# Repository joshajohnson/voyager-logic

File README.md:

# Voyager Logic

A FX3 based logic analyser capable of 16 channels at 100 MSPS.

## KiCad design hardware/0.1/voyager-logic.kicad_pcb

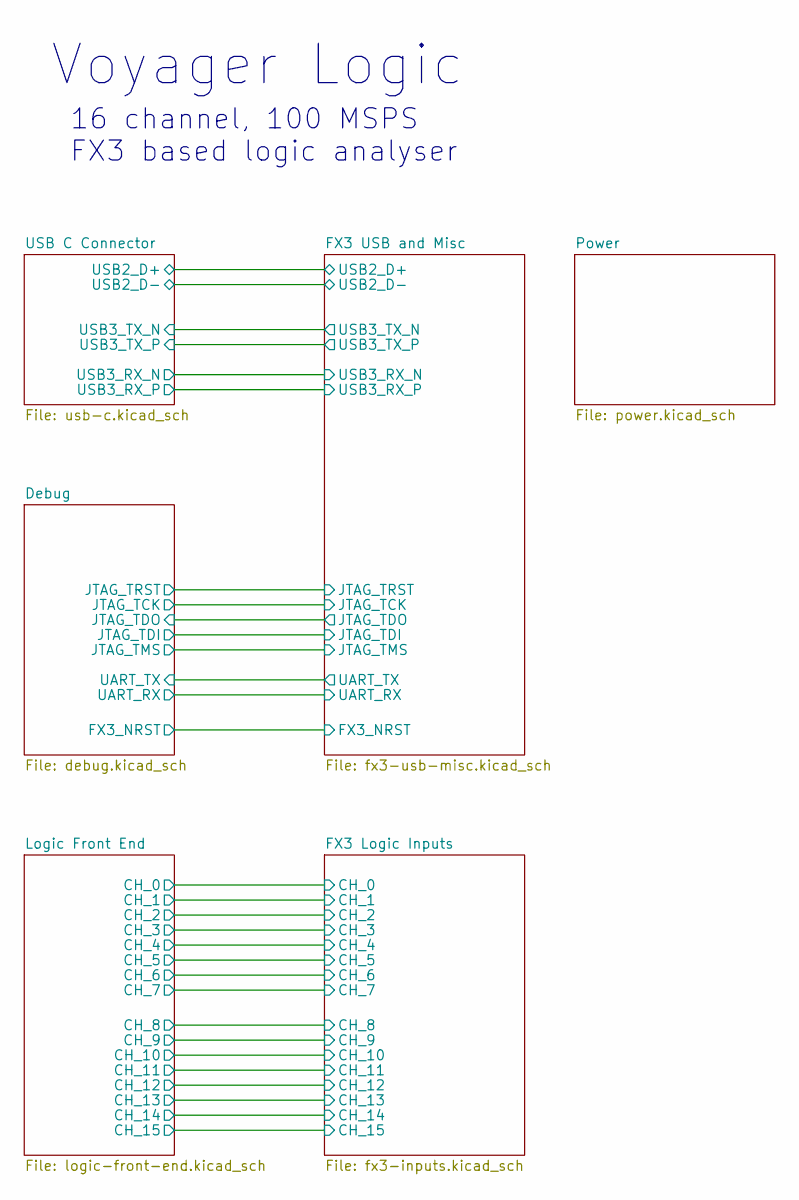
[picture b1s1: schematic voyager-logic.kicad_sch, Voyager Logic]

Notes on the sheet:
16 channel, 100 MSPS FX3 based logic analyser
Voyager Logic

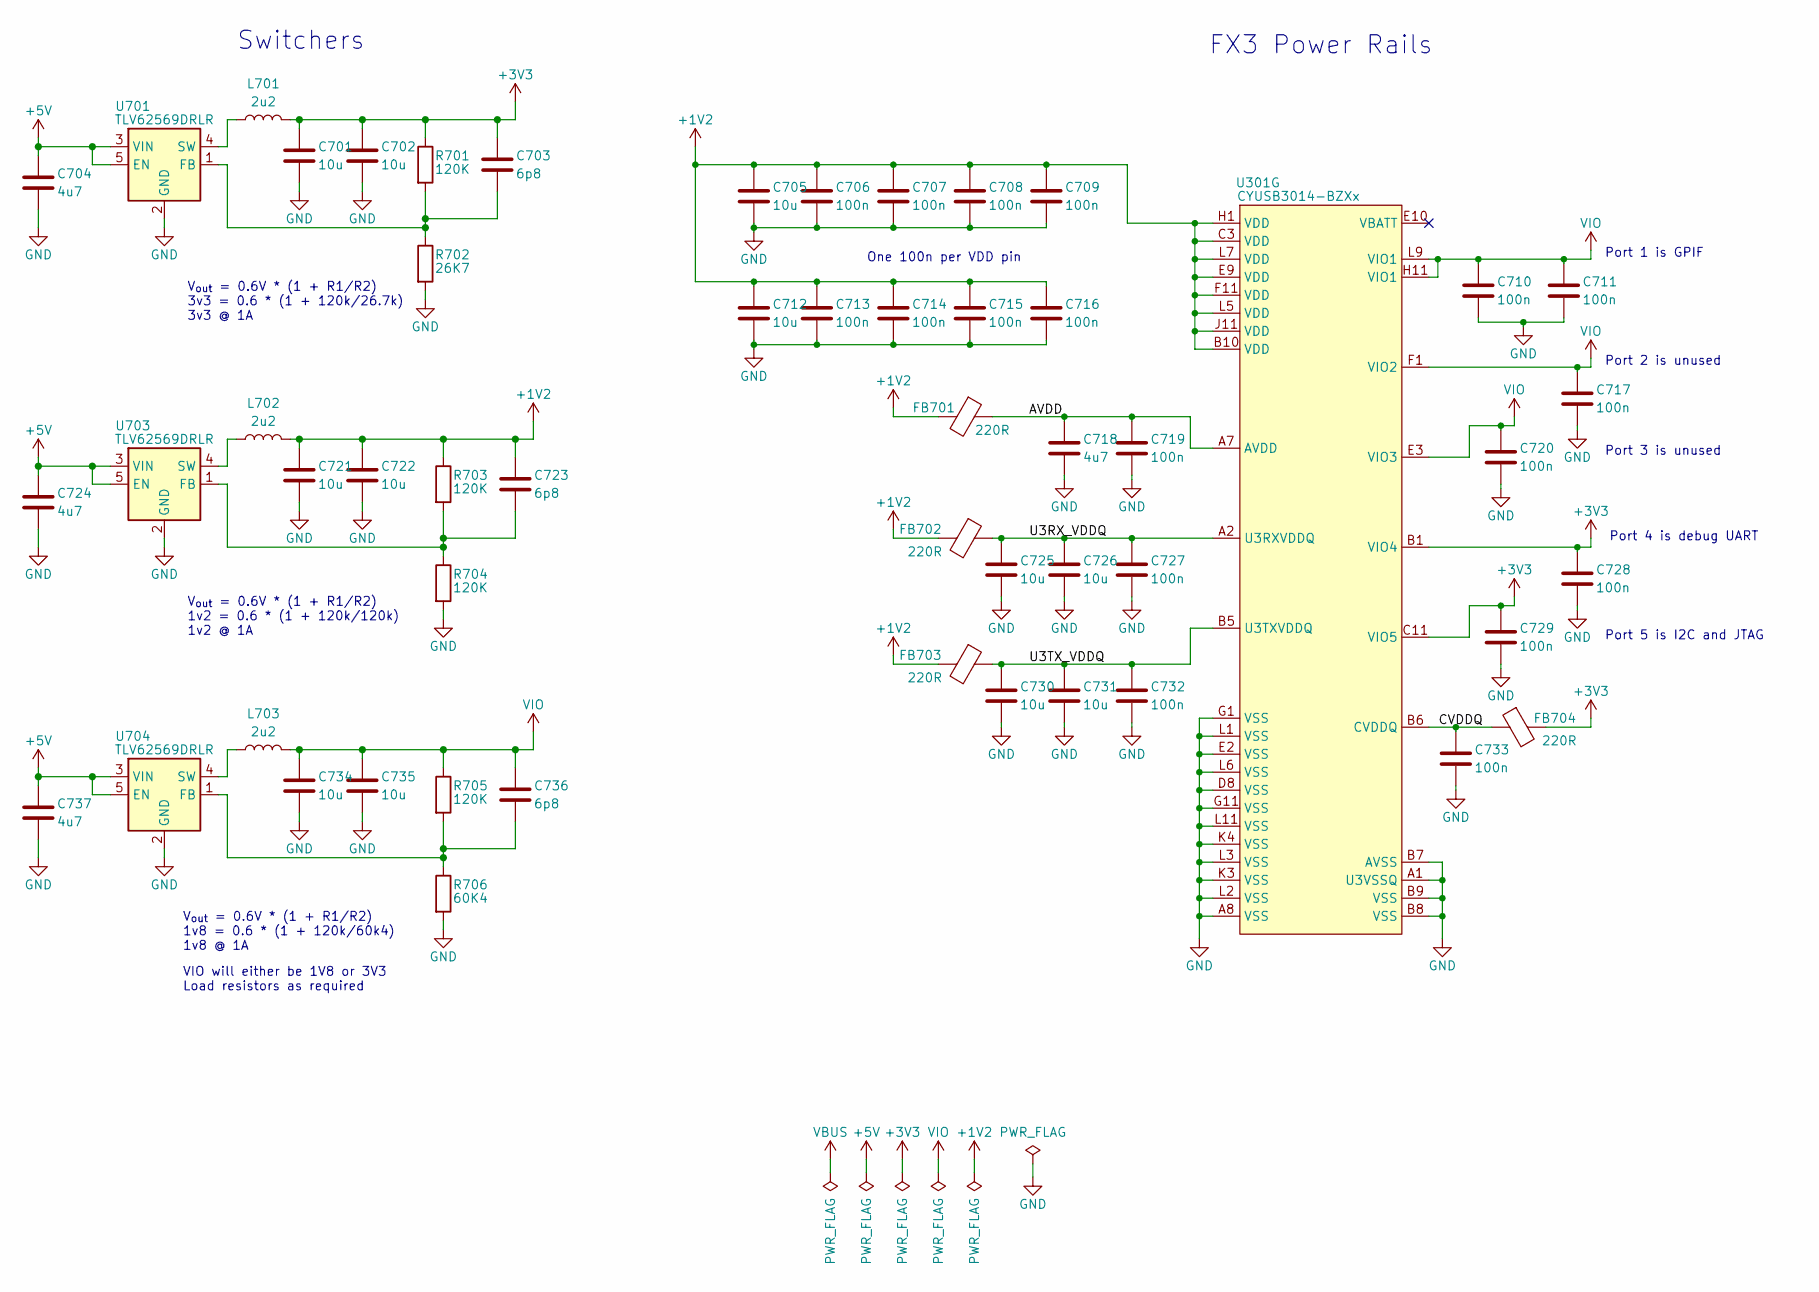
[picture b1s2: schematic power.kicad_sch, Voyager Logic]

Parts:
C701, C702, C705, C712, C721, C722, C725, C726, C730, C731, C734, C735: 10u; C_0603_1608Metric; MPN CL10A106MA8NRNC; LCSC C96446
C703, C723, C736: 6p8; C_0402_1005Metric; MPN GJM1555C1H6R8BB01D; LCSC C88896
C704, C718, C724, C737: 4u7; C_0402_1005Metric; MPN CL05A475MP5NRNC; LCSC C23733
C706, C707, C708, C709, C710, C711, C713, C714, C715, C716, C717, C719, C720, C727, C728, C729, C732, C733: 100n; C_0402_1005Metric; MPN CL05B104KB54PNC; LCSC C307331
FB701, FB702, FB703, FB704: 220R; R_0402_1005Metric; MPN BLM15PX221SN1D; LCSC C160973
L701, L702, L703: 2u2; L_0805_2012Metric; MPN LQM21PN2R2NGCD; LCSC C216156
R701, R703, R704, R705: 120K; R_0402_1005Metric; MPN RC0402FR-07120KL; LCSC C93945
R702: 26K7; R_0402_1005Metric; MPN RC0402FR-0726K7L; LCSC C138023
R706: 60K4; R_0402_1005Metric; MPN RC0402FR-0760K4L; LCSC C327333
U301: CYUSB3014-BZXx; BGA-121_10x10mm_Layout11x11_P0.8mm; MPN CYUSB3014-BZXC; LCSC C462526
U701, U703, U704: TLV62569DRLR; SOT-563; MPN TLV62569DRLR; LCSC C163217

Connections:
+1V2: C705.1, C706.1, C707.1, C708.1, C709.1, C712.1, C713.1, C714.1, C715.1, C716.1, C721.1, C722.1, C723.1, FB701.2, FB702.2, FB703.2, L702.2, R703.1, U301.B10 (VDD), U301.C3 (VDD), U301.E9 (VDD), U301.F11 (VDD), U301.H1 (VDD), U301.J11 (VDD), U301.L5 (VDD), U301.L7 (VDD)
+3V3: C701.1, C702.1, C703.1, C728.1, C729.1, FB704.2, L701.2, R701.1, U301.B1 (VIO4), U301.C11 (VIO5); also elsewhere on the board
+5V: C704.1, C724.1, C737.1, U701.3 (VIN), U701.5 (EN), U703.3 (VIN), U703.5 (EN), U704.3 (VIN), U704.5 (EN); also elsewhere on the board
/Power/AVDD: C718.1, C719.1, FB701.1, U301.A7 (AVDD)
/Power/CVDDQ: C733.1, FB704.1, U301.B6 (CVDDQ)
/Power/U3RX_VDDQ: C725.1, C726.1, C727.1, FB702.1, U301.A2 (U3RXVDDQ)
/Power/U3TX_VDDQ: C730.1, C731.1, C732.1, FB703.1, U301.B5 (U3TXVDDQ)
GND: C701.2, C702.2, C704.2, C705.2, C706.2, C707.2, C708.2, C709.2, C710.2, C711.2, C712.2, C713.2, C714.2, C715.2, C716.2, C717.2, C718.2, C719.2, C720.2, C721.2, C722.2, C724.2, C725.2, C726.2, C727.2, C728.2, C729.2, C730.2, C731.2, C732.2, C733.2, C734.2, C735.2, C737.2, R702.2, R704.2, R706.2, U301.A1 (U3VSSQ), U301.A8 (VSS), U301.B7 (AVSS), U301.B8 (VSS), U301.B9 (VSS), U301.D8 (VSS), U301.E2 (VSS), U301.G1 (VSS), U301.G11 (VSS), U301.K3 (VSS), U301.K4 (VSS), U301.L1 (VSS), U301.L2 (VSS), U301.L3 (VSS), U301.L6 (VSS), U301.L11 (VSS), U701.2 (GND), U703.2 (GND), U704.2 (GND); also elsewhere on the board
unnamed: C703.2, R701.2, R702.1, U701.1 (FB)
unnamed: C723.2, R703.2, R704.1, U703.1 (FB)
unnamed: C736.2, R705.2, R706.1, U704.1 (FB)
unnamed: L701.1, U701.4 (SW)
unnamed: L702.1, U703.4 (SW)
unnamed: L703.1, U704.4 (SW)
VIO: C710.1, C711.1, C717.1, C720.1, C734.1, C735.1, C736.1, L703.2, R705.1, U301.E3 (VIO3), U301.F1 (VIO2), U301.H11 (VIO1), U301.L9 (VIO1); also elsewhere on the board

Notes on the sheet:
V_{out} = 0.6V * (1 + R1/R2) 3v3 = 0.6 * (1 + 120k/26.7k) 3v3 @ 1A
V_{out} = 0.6V * (1 + R1/R2) 1v8 = 0.6 * (1 + 120k/60k4) 1v8 @ 1A
Switchers
FX3 Power Rails
Port 2 is unused
Port 4 is debug UART
One 100n per VDD pin
Port 3 is unused
V_{out} = 0.6V * (1 + R1/R2) 1v2 = 0.6 * (1 + 120k/120k) 1v2 @ 1A
Port 1 is GPIF
Port 5 is I2C and JTAG
VIO will either be 1V8 or 3V3 Load resistors as required

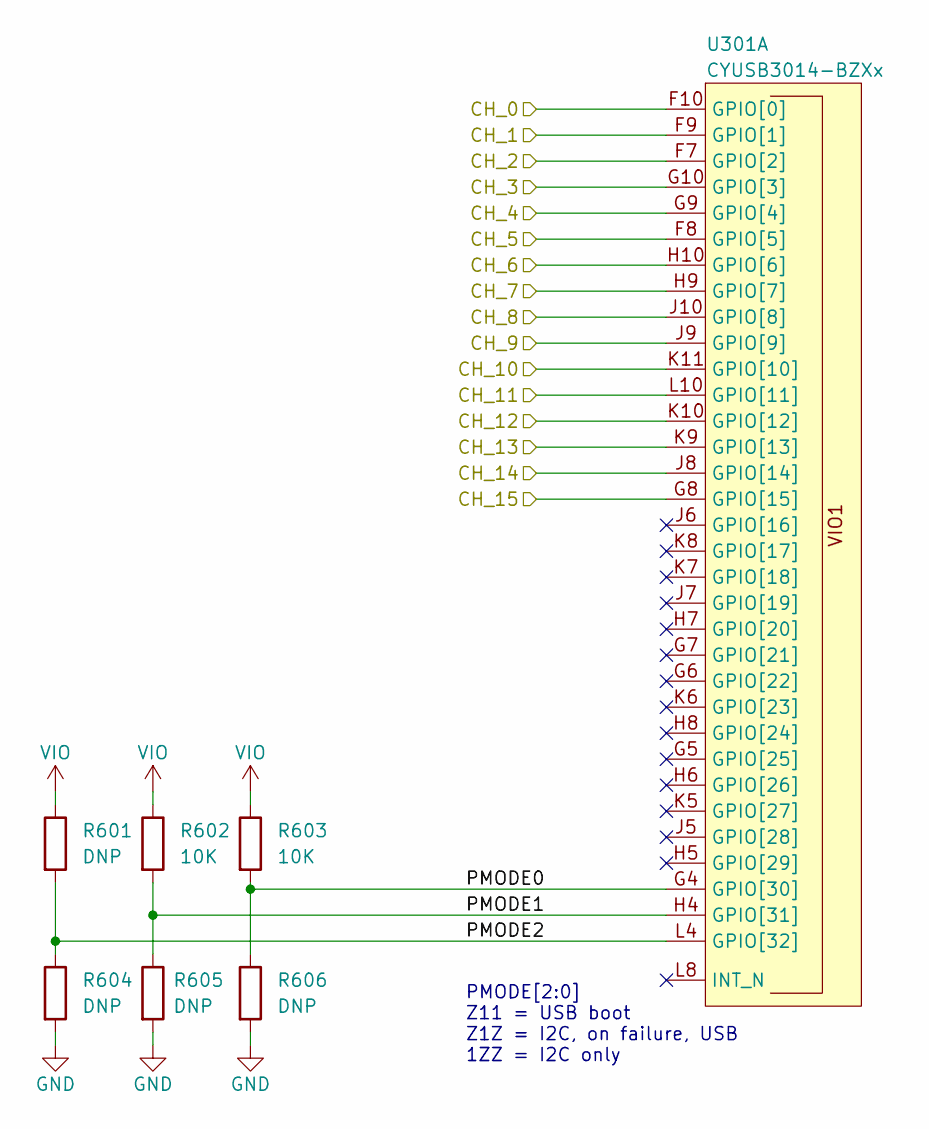
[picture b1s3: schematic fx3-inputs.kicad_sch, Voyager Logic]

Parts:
R601, R604, R605, R606: DNP; R_0402_1005Metric
R602, R603: 10K; R_0402_1005Metric; MPN RC0402FR-0710KL; LCSC C60490
U301: CYUSB3014-BZXx; BGA-121_10x10mm_Layout11x11_P0.8mm; MPN CYUSB3014-BZXC; LCSC C462526

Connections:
/FX3 Logic Inputs/CH_0: U301.F10 (GPIO[0]); also elsewhere on the board
/FX3 Logic Inputs/CH_1: U301.F9 (GPIO[1]); also elsewhere on the board
/FX3 Logic Inputs/CH_2: U301.F7 (GPIO[2]); also elsewhere on the board
/FX3 Logic Inputs/CH_3: U301.G10 (GPIO[3]); also elsewhere on the board
/FX3 Logic Inputs/CH_4: U301.G9 (GPIO[4]); also elsewhere on the board
/FX3 Logic Inputs/CH_5: U301.F8 (GPIO[5]); also elsewhere on the board
/FX3 Logic Inputs/CH_6: U301.H10 (GPIO[6]); also elsewhere on the board
/FX3 Logic Inputs/CH_7: U301.H9 (GPIO[7]); also elsewhere on the board
/FX3 Logic Inputs/CH_8: U301.J10 (GPIO[8]); also elsewhere on the board
/FX3 Logic Inputs/CH_9: U301.J9 (GPIO[9]); also elsewhere on the board
/FX3 Logic Inputs/CH_10: U301.K11 (GPIO[10]); also elsewhere on the board
/FX3 Logic Inputs/CH_11: U301.L10 (GPIO[11]); also elsewhere on the board
/FX3 Logic Inputs/CH_12: U301.K10 (GPIO[12]); also elsewhere on the board
/FX3 Logic Inputs/CH_13: U301.K9 (GPIO[13]); also elsewhere on the board
/FX3 Logic Inputs/CH_14: U301.J8 (GPIO[14]); also elsewhere on the board
/FX3 Logic Inputs/CH_15: U301.G8 (GPIO[15]); also elsewhere on the board
/FX3 Logic Inputs/PMODE0: R603.2, R606.1, U301.G4 (GPIO[30])
/FX3 Logic Inputs/PMODE1: R602.2, R605.1, U301.H4 (GPIO[31])
/FX3 Logic Inputs/PMODE2: R601.2, R604.1, U301.L4 (GPIO[32])
GND: R604.2, R605.2, R606.2; also elsewhere on the board
VIO: R601.1, R602.1, R603.1; also elsewhere on the board

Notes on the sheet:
PMODE[2:0] Z11 = USB boot Z1Z = I2C, on failure, USB 1ZZ = I2C only

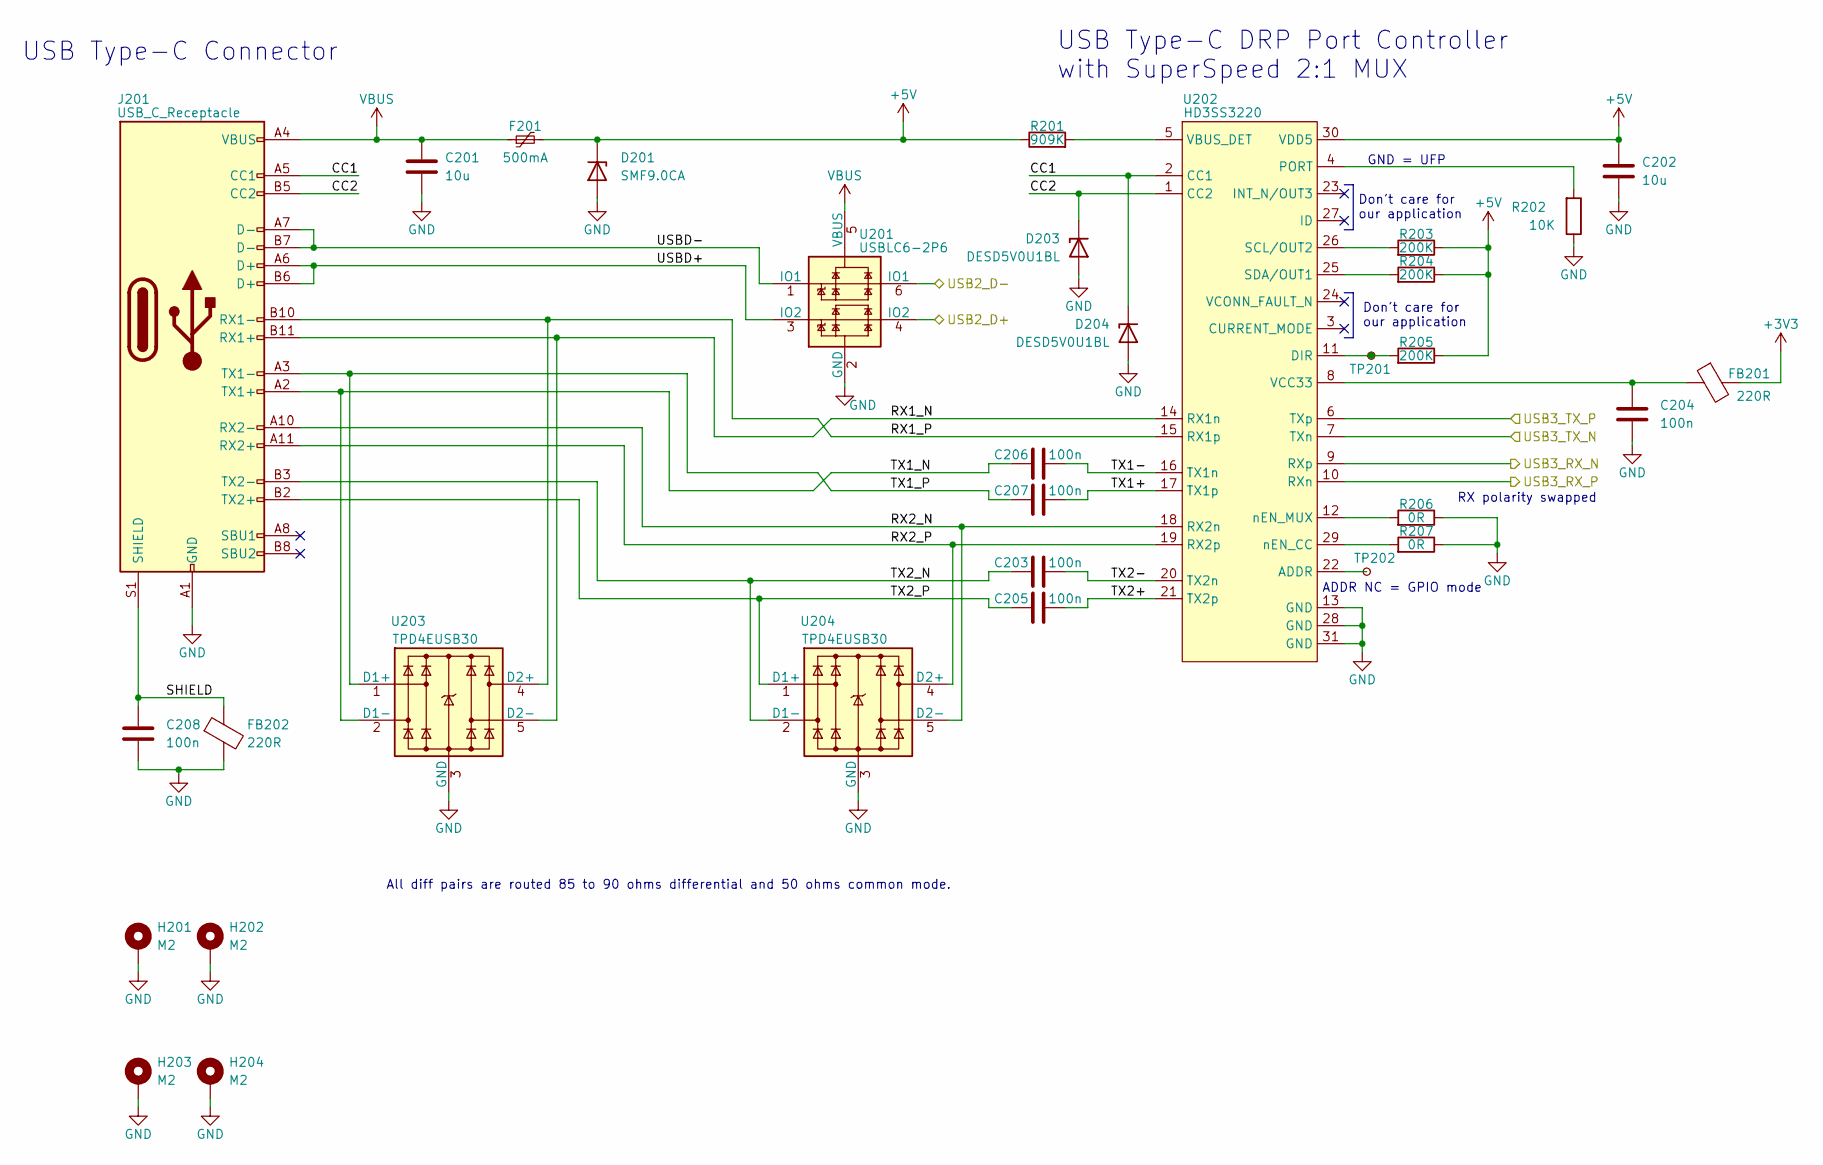
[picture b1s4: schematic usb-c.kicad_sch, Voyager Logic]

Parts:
C201, C202: 10u; C_0603_1608Metric; MPN CL10A106MA8NRNC; LCSC C96446
C203, C205, C206, C207: 100n; C_0201_0603Metric; MPN CL03A104KO3NNNC; LCSC C307380
C204, C208: 100n; C_0402_1005Metric; MPN CL05B104KB54PNC; LCSC C307331
D201: SMF9.0CA; D_SOD-123FL; MPN SMF9.0CA; Digikey 18-SMF9.0CACT-ND
D203, D204: DESD5V0U1BL; D_X1-DFN1006-2; MPN DESD5V0U1BL-7B; Digikey 31-DESD5V0U1BL-7BCT-ND
F201: 500mA; Fuse_0805_2012Metric; MPN SMD0805-050; LCSC C66452
FB201, FB202: 220R; R_0402_1005Metric; MPN BLM15PX221SN1D; LCSC C160973
H201, H202, H203, H204: M2; MountingHole_2.2mm_M2_ISO7380_Pad
J201: USB_C_Receptacle; USB_C_Receptacle_Amphenol_10137062-00021LF; MPN 10137062-00021LF; Digikey 609-6109-1-ND
R201: 909K; R_0402_1005Metric; MPN AC0402FR-07909KL; LCSC C227267
R202: 10K; R_0402_1005Metric; MPN RC0402FR-0710KL; LCSC C60490
R203, R204, R205: 200K; R_0402_1005Metric; MPN RC0402FR-07200KL; LCSC C114763
R206, R207: 0R; R_0402_1005Metric; MPN RC0402FR-070RL; LCSC C106231
TP201, TP202: TP; TestPoint_SMDPad_D0.5mm_NO_SILK
U201: USBLC6-2P6; SOT-563; MPN USBLC6-2P6; LCSC C15999
U202: HD3SS3220; Texas_RNH0030A_WQFN-30_2.5x4.5mm_P0.4mm; MPN HD3SS3220RN; Digikey 296-48293-1-ND
U203, U204: TPD4EUSB30; USON-10_2.5x1.0mm_P0.5mm; MPN TPD4EUSB30DQAR; Digikey 296-28063-1-ND

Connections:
+3V3: FB201.2; also elsewhere on the board
+5V: C202.1, D201.1 (K), F201.2, R201.1, R203.1, R204.1, R205.1, U202.30 (VDD5); also elsewhere on the board
/FX3 USB and Misc/USB2_D+: U201.4 (IO2); also elsewhere on the board
/FX3 USB and Misc/USB2_D-: U201.6 (IO1); also elsewhere on the board
/FX3 USB and Misc/USB3_RX_N: U202.9 (RXp); also elsewhere on the board
/FX3 USB and Misc/USB3_RX_P: U202.10 (RXn); also elsewhere on the board
/FX3 USB and Misc/USB3_TX_N: U202.7 (TXn); also elsewhere on the board
/FX3 USB and Misc/USB3_TX_P: U202.6 (TXp); also elsewhere on the board
/USB C Connector/CC1: D204.1 (K), J201.A5 (CC1), U202.2 (CC1)
/USB C Connector/CC2: D203.1 (K), J201.B5 (CC2), U202.1 (CC2)
/USB C Connector/RX1_N: J201.B11 (RX1+), U202.14 (RX1n), U203.5 (D2-), U203.6 (NC)
/USB C Connector/RX1_P: J201.B10 (RX1-), U202.15 (RX1p), U203.4 (D2+), U203.7 (NC)
/USB C Connector/RX2_N: J201.A10 (RX2-), U202.18 (RX2n), U204.5 (D2-), U204.6 (NC)
/USB C Connector/RX2_P: J201.A11 (RX2+), U202.19 (RX2p), U204.4 (D2+), U204.7 (NC)
/USB C Connector/SHIELD: C208.1, FB202.1, J201.S1 (SHIELD)
/USB C Connector/TX1+: C207.2, U202.17 (TX1p)
/USB C Connector/TX1-: C206.2, U202.16 (TX1n)
/USB C Connector/TX1_N: C206.1, J201.A2 (TX1+), U203.2 (D1-), U203.9 (NC)
/USB C Connector/TX1_P: C207.1, J201.A3 (TX1-), U203.1 (D1+), U203.10 (NC)
/USB C Connector/TX2+: C205.2, U202.21 (TX2p)
/USB C Connector/TX2-: C203.2, U202.20 (TX2n)
/USB C Connector/TX2_N: C203.1, J201.B3 (TX2-), U204.2 (D1-), U204.9 (NC)
/USB C Connector/TX2_P: C205.1, J201.B2 (TX2+), U204.1 (D1+), U204.10 (NC)
/USB C Connector/USBD+: J201.A6 (D+), J201.B6 (D+), U201.3 (IO2)
/USB C Connector/USBD-: J201.A7 (D-), J201.B7 (D-), U201.1 (IO1)
GND: C201.2, C202.2, C204.2, C208.2, D201.2 (A), D203.2 (A), D204.2 (A), FB202.2, H201.1, H202.1, H203.1, H204.1, J201.A1 (GND), J201.A12 (GND), J201.B1 (GND), J201.B12 (GND), R202.1, R206.1, R207.1, U201.2 (GND), U202.13 (GND), U202.28 (GND), U202.31 (GND), U203.3 (GND), U203.8 (GND), U204.3 (GND), U204.8 (GND); also elsewhere on the board
unnamed: C204.1, FB201.1, U202.8 (VCC33)
unnamed: R201.2, U202.5 (VBUS_DET)
unnamed: R202.2, U202.4 (PORT)
unnamed: R203.2, U202.26 (SCL/OUT2)
unnamed: R204.2, U202.25 (SDA/OUT1)
unnamed: R205.2, TP201.1, U202.11 (DIR)
unnamed: R206.2, U202.12 (nEN_MUX)
unnamed: R207.2, U202.29 (nEN_CC)
unnamed: TP202.1, U202.22 (ADDR)
VBUS: C201.1, F201.1, J201.A4 (VBUS), J201.A9 (VBUS), J201.B4 (VBUS), J201.B9 (VBUS), U201.5 (VBUS)

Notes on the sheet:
Don't care for our application
RX polarity swapped
ADDR NC = GPIO mode
GND = UFP
USB Type-C Connector
All diff pairs are routed 85 to 90 ohms differential and 50 ohms common mode.
USB Type-C DRP Port Controller with SuperSpeed 2:1 MUX

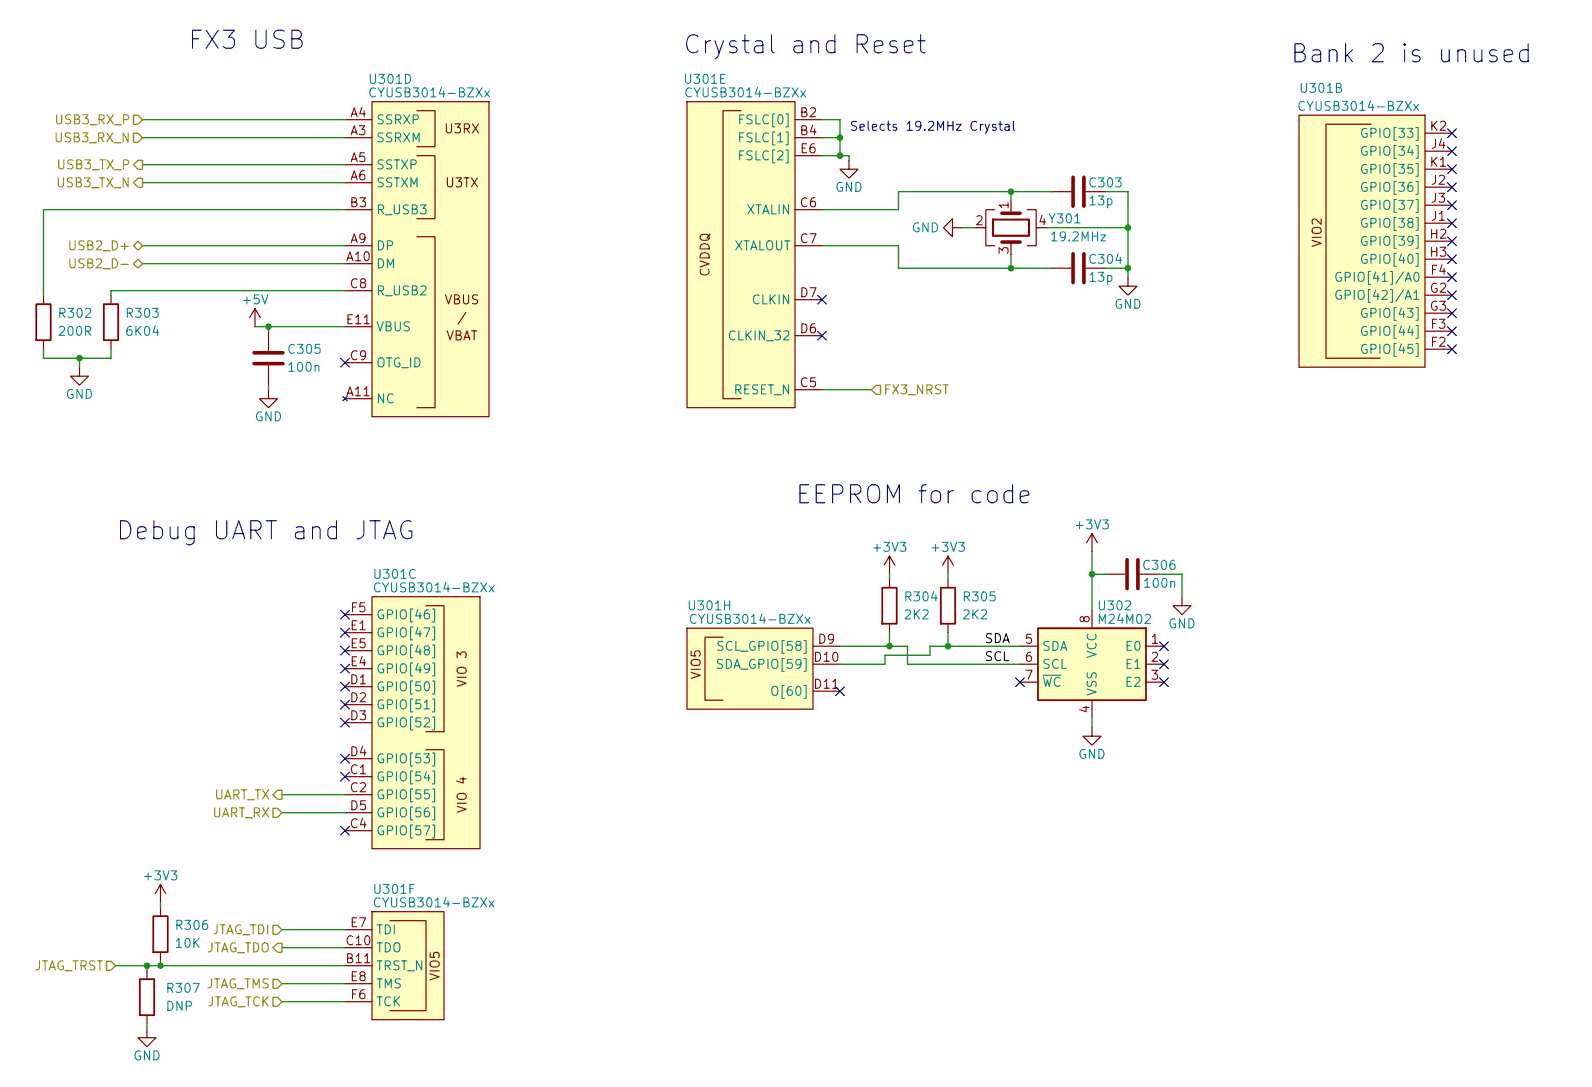
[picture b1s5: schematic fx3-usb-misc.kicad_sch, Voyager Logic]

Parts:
C303, C304: 13p; C_0402_1005Metric; MPN GCM1555C1H130JA16D; LCSC C2195053
C305, C306: 100n; C_0402_1005Metric; MPN CL05B104KB54PNC; LCSC C307331
R302: 200R; R_0402_1005Metric; MPN RC0402FR-07200RL; LCSC C114764
R303: 6K04; R_0402_1005Metric; MPN AC0402FR-076K04L; LCSC C144739
R304, R305: 2K2; R_0402_1005Metric; MPN RC0402FR-072K2L; LCSC C114762
R306: 10K; R_0402_1005Metric; MPN RC0402FR-0710KL; LCSC C60490
R307: DNP; R_0402_1005Metric
U301: CYUSB3014-BZXx; BGA-121_10x10mm_Layout11x11_P0.8mm; MPN CYUSB3014-BZXC; LCSC C462526
U302: M24M02; SOIC-8_3.9x4.9mm_P1.27mm; MPN M24M02-DRMN6TP; LCSC C115042
Y301: 19.2MHz; Crystal_SMD_2520-4Pin_2.5x2.0mm; MPN EXS00A-CS05400; Digikey 644-1162-2-ND

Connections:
+3V3: C306.1, R304.1, R305.1, R306.1, U302.8 (VCC); also elsewhere on the board
+5V: C305.1, U301.E11 (VBUS); also elsewhere on the board
/Debug/FX3_NRST: U301.C5 (RESET_N); also elsewhere on the board
/Debug/JTAG_TCK: U301.F6 (TCK); also elsewhere on the board
/Debug/JTAG_TDI: U301.E7 (TDI); also elsewhere on the board
/Debug/JTAG_TDO: U301.C10 (TDO); also elsewhere on the board
/Debug/JTAG_TMS: U301.E8 (TMS); also elsewhere on the board
/Debug/JTAG_TRST: R306.2, R307.1, U301.B11 (TRST_N); also elsewhere on the board
/Debug/UART_RX: U301.D5 (GPIO[56]); also elsewhere on the board
/Debug/UART_TX: U301.C2 (GPIO[55]); also elsewhere on the board
/FX3 USB and Misc/SCL: R304.2, U301.D9 (SCL_GPIO[58]), U302.6 (SCL)
/FX3 USB and Misc/SDA: R305.2, U301.D10 (SDA_GPIO[59]), U302.5 (SDA)
/FX3 USB and Misc/USB2_D+: U301.A9 (DP); also elsewhere on the board
/FX3 USB and Misc/USB2_D-: U301.A10 (DM); also elsewhere on the board
/FX3 USB and Misc/USB3_RX_N: U301.A3 (SSRXM); also elsewhere on the board
/FX3 USB and Misc/USB3_RX_P: U301.A4 (SSRXP); also elsewhere on the board
/FX3 USB and Misc/USB3_TX_N: U301.A6 (SSTXM); also elsewhere on the board
/FX3 USB and Misc/USB3_TX_P: U301.A5 (SSTXP); also elsewhere on the board
GND: C303.2, C304.2, C305.2, C306.2, R302.2, R303.2, R307.2, U301.B2 (FSLC[0]), U301.B4 (FSLC[1]), U301.E6 (FSLC[2]), U302.4 (VSS), Y301.2, Y301.4; also elsewhere on the board
unnamed: C303.1, U301.C6 (XTALIN), Y301.1
unnamed: C304.1, U301.C7 (XTALOUT), Y301.3
unnamed: R302.1, U301.B3 (R_USB3)
unnamed: R303.1, U301.C8 (R_USB2)

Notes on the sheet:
Crystal and Reset
Selects 19.2MHz Crystal
FX3 USB
Debug UART and JTAG
EEPROM for code
Bank 2 is unused

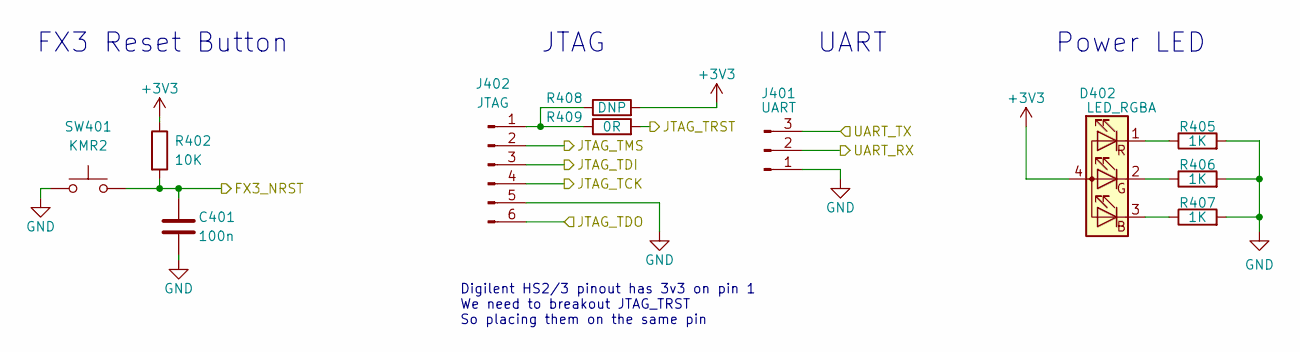
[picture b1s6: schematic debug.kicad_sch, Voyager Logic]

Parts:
C401: 100n; C_0402_1005Metric; MPN CL05B104KB54PNC; LCSC C307331
D402: LED_RGBA; LED_TRI_2020; MPN FM-B2020RGBA-HG; LCSC C108793
J401: UART; 3_PIN_THT_Staggered
J402: JTAG; 6_PIN_THT_Staggered
R402: 10K; R_0402_1005Metric; MPN RC0402FR-0710KL; LCSC C60490
R405, R406, R407: 1K; R_0402_1005Metric; MPN AC0402FR-071KL; LCSC C144789
R408: DNP; R_0402_1005Metric
R409: 0R; R_0402_1005Metric; MPN RC0402FR-070RL; LCSC C106231
SW401: KMR2; SW_Push_KMR2; MPN KMR233GLFG; LCSC C2689601

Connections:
+3V3: D402.4 (A), R402.1, R408.2; also elsewhere on the board
/Debug/FX3_NRST: C401.1, R402.2, SW401.2; also elsewhere on the board
/Debug/JTAG_TCK: J402.4; also elsewhere on the board
/Debug/JTAG_TDI: J402.3; also elsewhere on the board
/Debug/JTAG_TDO: J402.6; also elsewhere on the board
/Debug/JTAG_TMS: J402.2; also elsewhere on the board
/Debug/JTAG_TRST: R409.2; also elsewhere on the board
/Debug/UART_RX: J401.2; also elsewhere on the board
/Debug/UART_TX: J401.3; also elsewhere on the board
GND: C401.2, J401.1, J402.5, R405.2, R406.2, R407.2, SW401.1; also elsewhere on the board
unnamed: D402.1 (RK), R405.1
unnamed: D402.2 (GK), R406.1
unnamed: D402.3 (BK), R407.1
unnamed: J402.1, R408.1, R409.1

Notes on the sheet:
Power LED
UART
Digilent HS2/3 pinout has 3v3 on pin 1 We need to breakout JTAG_TRST So placing them on the same pin
FX3 Reset Button
JTAG

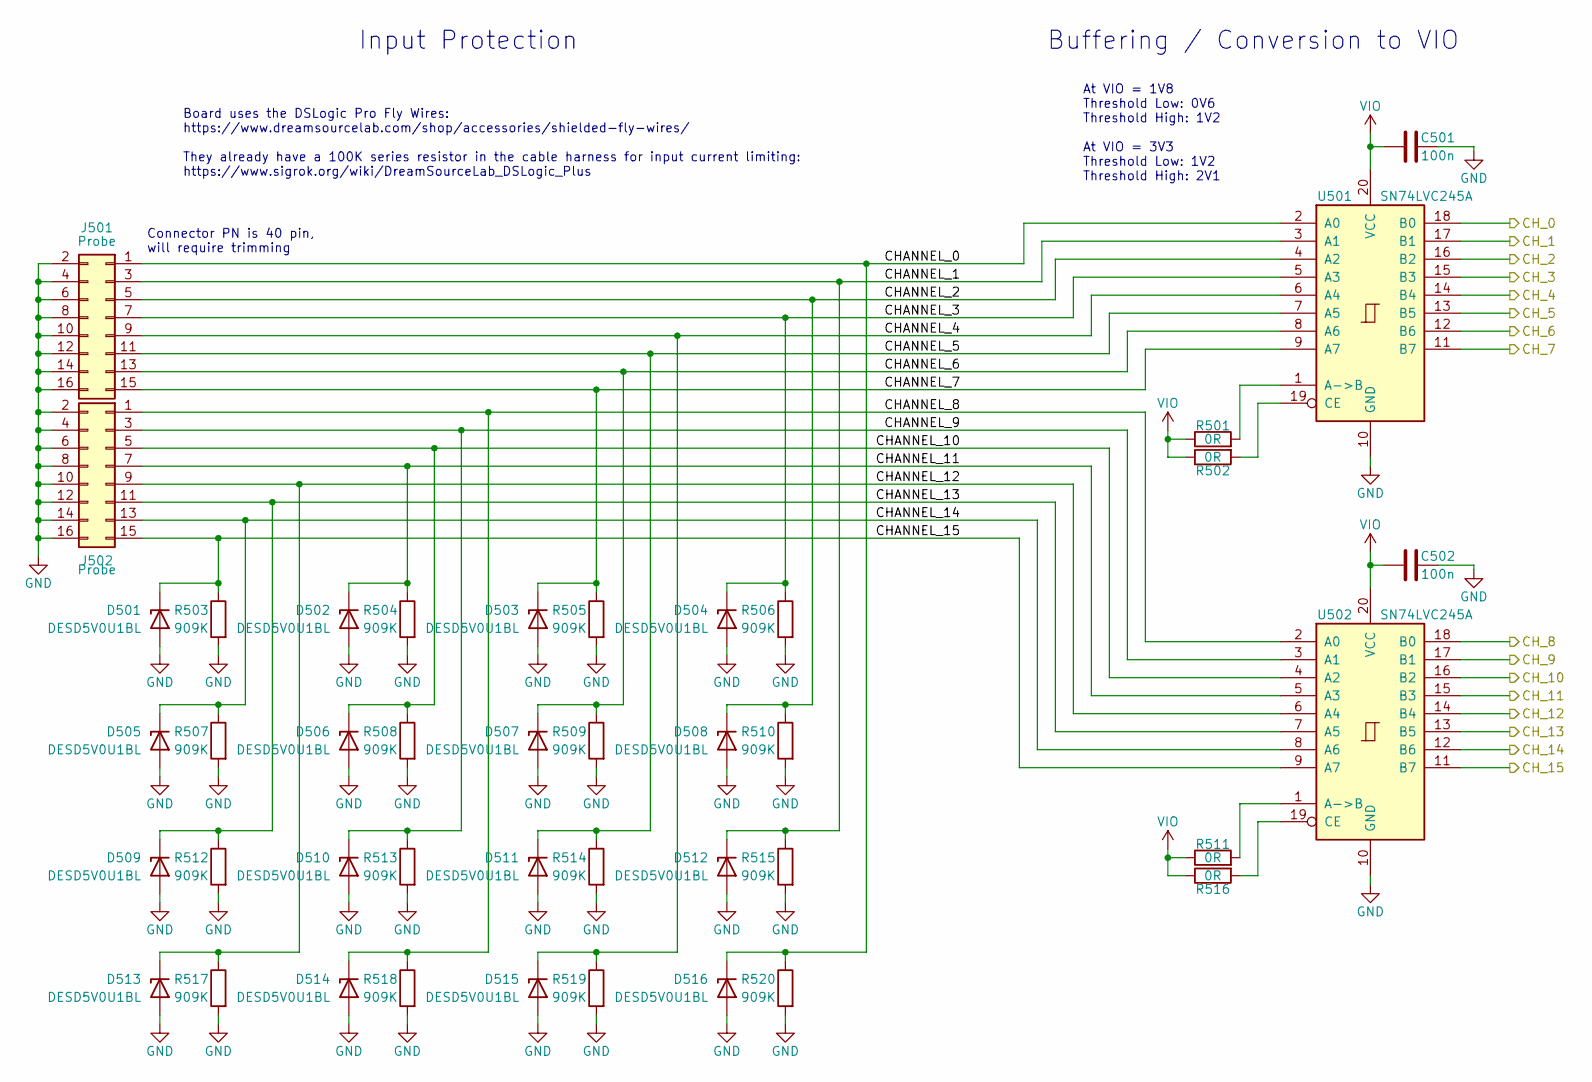
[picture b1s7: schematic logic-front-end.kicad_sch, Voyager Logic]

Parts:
C501, C502: 100n; C_0402_1005Metric; MPN CL05B104KB54PNC; LCSC C307331
D501, D502, D503, D504, D505, D506, D507, D508, D509, D510, D511, D512, D513, D514, D515, D516: DESD5V0U1BL; D_X1-DFN1006-2; MPN DESD5V0U1BL-7B; Digikey 31-DESD5V0U1BL-7BCT-ND
J501, J502: Probe; PinSocket_2x08_P1.27mm_Horizontal
R501, R502, R511, R516: 0R; R_0402_1005Metric; MPN RC0402FR-070RL; LCSC C106231
R503, R504, R505, R506, R507, R508, R509, R510, R512, R513, R514, R515, R517, R518, R519, R520: 909K; R_0402_1005Metric; MPN AC0402FR-07909KL; LCSC C227267
U501, U502: SN74LVC245A; TSSOP-20_4.4x6.5mm_P0.65mm; MPN SN74LVC245ARGYR; Digikey SN74LVC245ARGYR

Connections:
/FX3 Logic Inputs/CH_0: U501.18 (B0); also elsewhere on the board
/FX3 Logic Inputs/CH_1: U501.17 (B1); also elsewhere on the board
/FX3 Logic Inputs/CH_2: U501.16 (B2); also elsewhere on the board
/FX3 Logic Inputs/CH_3: U501.15 (B3); also elsewhere on the board
/FX3 Logic Inputs/CH_4: U501.14 (B4); also elsewhere on the board
/FX3 Logic Inputs/CH_5: U501.13 (B5); also elsewhere on the board
/FX3 Logic Inputs/CH_6: U501.12 (B6); also elsewhere on the board
/FX3 Logic Inputs/CH_7: U501.11 (B7); also elsewhere on the board
/FX3 Logic Inputs/CH_8: U502.18 (B0); also elsewhere on the board
/FX3 Logic Inputs/CH_9: U502.17 (B1); also elsewhere on the board
/FX3 Logic Inputs/CH_10: U502.16 (B2); also elsewhere on the board
/FX3 Logic Inputs/CH_11: U502.15 (B3); also elsewhere on the board
/FX3 Logic Inputs/CH_12: U502.14 (B4); also elsewhere on the board
/FX3 Logic Inputs/CH_13: U502.13 (B5); also elsewhere on the board
/FX3 Logic Inputs/CH_14: U502.12 (B6); also elsewhere on the board
/FX3 Logic Inputs/CH_15: U502.11 (B7); also elsewhere on the board
/Logic Front End/CHANNEL_0: D516.1 (K), J501.1, R520.1, U501.2 (A0)
/Logic Front End/CHANNEL_1: D512.1 (K), J501.3, R515.1, U501.3 (A1)
/Logic Front End/CHANNEL_2: D508.1 (K), J501.5, R510.1, U501.4 (A2)
/Logic Front End/CHANNEL_3: D504.1 (K), J501.7, R506.1, U501.5 (A3)
/Logic Front End/CHANNEL_4: D515.1 (K), J501.9, R519.1, U501.6 (A4)
/Logic Front End/CHANNEL_5: D511.1 (K), J501.11, R514.1, U501.7 (A5)
/Logic Front End/CHANNEL_6: D507.1 (K), J501.13, R509.1, U501.8 (A6)
/Logic Front End/CHANNEL_7: D503.1 (K), J501.15, R505.1, U501.9 (A7)
/Logic Front End/CHANNEL_8: D514.1 (K), J502.1, R518.1, U502.2 (A0)
/Logic Front End/CHANNEL_9: D510.1 (K), J502.3, R513.1, U502.3 (A1)
/Logic Front End/CHANNEL_10: D506.1 (K), J502.5, R508.1, U502.4 (A2)
/Logic Front End/CHANNEL_11: D502.1 (K), J502.7, R504.1, U502.5 (A3)
/Logic Front End/CHANNEL_12: D513.1 (K), J502.9, R517.1, U502.6 (A4)
/Logic Front End/CHANNEL_13: D509.1 (K), J502.11, R512.1, U502.7 (A5)
/Logic Front End/CHANNEL_14: D505.1 (K), J502.13, R507.1, U502.8 (A6)
/Logic Front End/CHANNEL_15: D501.1 (K), J502.15, R503.1, U502.9 (A7)
GND: C501.2, C502.2, D501.2 (A), D502.2 (A), D503.2 (A), D504.2 (A), D505.2 (A), D506.2 (A), D507.2 (A), D508.2 (A), D509.2 (A), D510.2 (A), D511.2 (A), D512.2 (A), D513.2 (A), D514.2 (A), D515.2 (A), D516.2 (A), J501.2, J501.4, J501.6, J501.8, J501.10, J501.12, J501.14, J501.16, J502.2, J502.4, J502.6, J502.8, J502.10, J502.12, J502.14, J502.16, R503.2, R504.2, R505.2, R506.2, R507.2, R508.2, R509.2, R510.2, R512.2, R513.2, R514.2, R515.2, R517.2, R518.2, R519.2, R520.2, U501.10 (GND), U502.10 (GND); also elsewhere on the board
unnamed: R501.2, U501.1 (A->B)
unnamed: R502.2, U501.19 (CE)
unnamed: R511.2, U502.1 (A->B)
unnamed: R516.2, U502.19 (CE)
VIO: C501.1, C502.1, R501.1, R502.1, R511.1, R516.1, U501.20 (VCC), U502.20 (VCC); also elsewhere on the board

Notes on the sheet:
Buffering / Conversion to VIO
Board uses the DSLogic Pro Fly Wires: https://www.dreamsourcelab.com/shop/accessories/shielded-fly-wires/ They already have a 100K series resistor in the cable harness for input current limiting: https://www.sigrok.org/wiki/DreamSourceLab_DSLogic_Plus
Connector PN is 40 pin, will require trimming
At VIO = 1V8 Threshold Low: 0V6 Threshold High: 1V2 At VIO = 3V3 Threshold Low: 1V2 Threshold High: 2V1
Input Protection

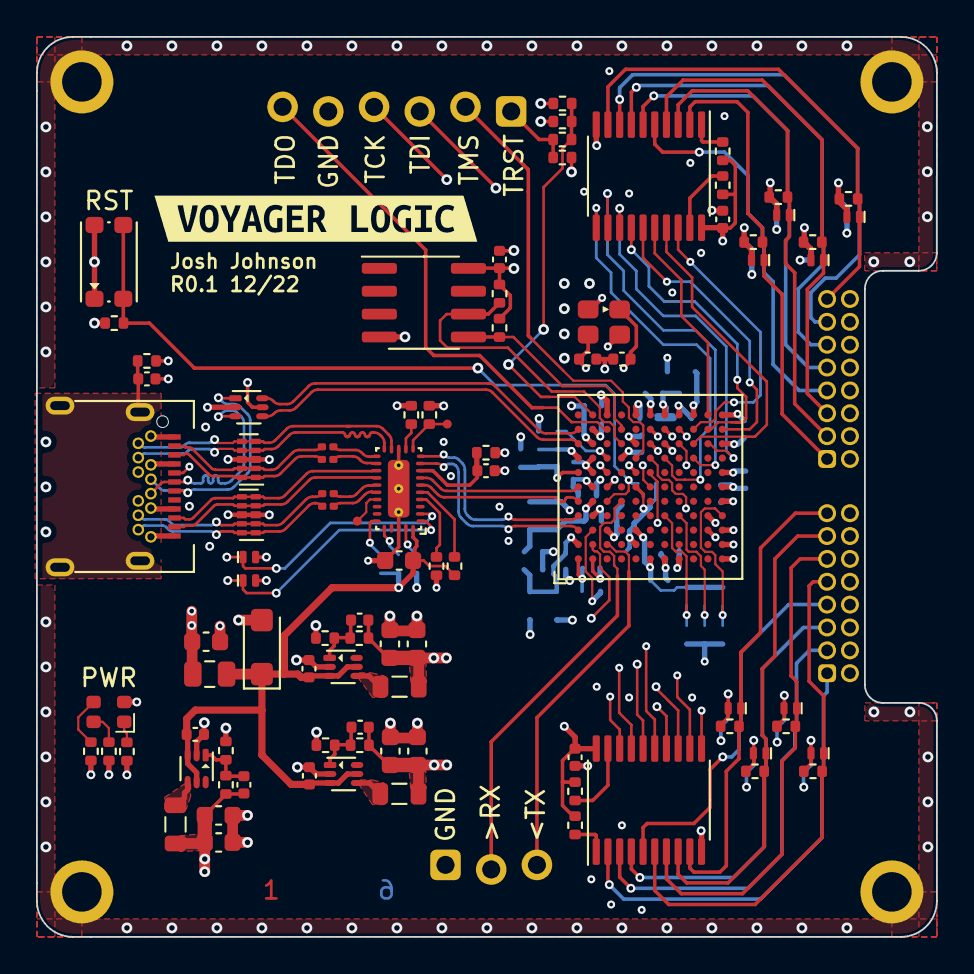
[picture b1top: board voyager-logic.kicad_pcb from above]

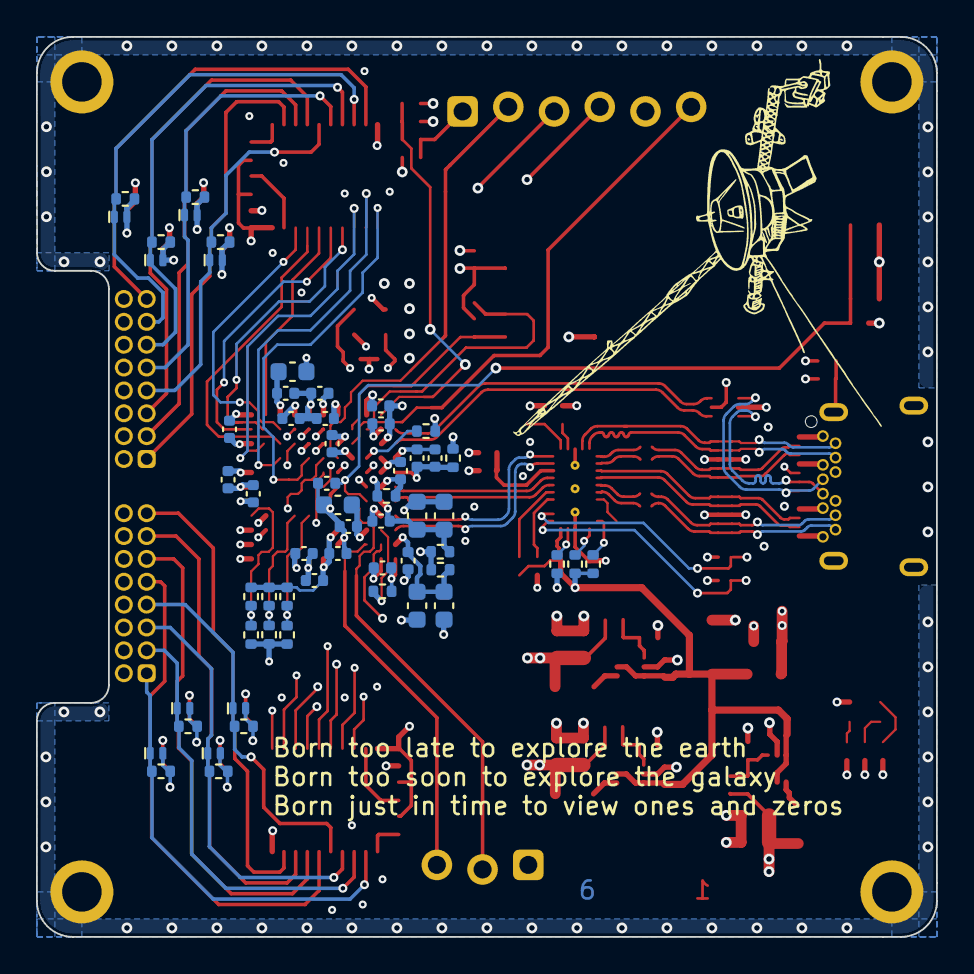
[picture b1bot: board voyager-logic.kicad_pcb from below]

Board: 6 copper layers, 50.0 x 50.0 mm, 158 parts (58 on the bottom side), 105 nets.

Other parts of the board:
kibuzzard-63948718: G***; kibuzzard-63948718

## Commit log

2022-11-22 setup template
2022-11-24 wip usb c design
2022-11-25 continue schematic design
2022-11-26 first pass schematic done
2022-11-27 finalise BOM
2022-11-29 all components fit inside outline
2022-12-05 break out bga
2022-12-06 more io routing
2022-12-10 usb3 routed less tuning
2022-12-10 wip, switchers todo
2022-12-11 erc = drc = 0, fixup BOM
2022-12-21 component shortage changes
2022-12-25 clean up everything but usb3
2022-12-25 usb 3 clean up
